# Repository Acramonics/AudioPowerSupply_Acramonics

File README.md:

Audio Power Supply
==================

(c) acramonics July 2026
------------------------

This audio power supply is a simple 15-0-15V supply using a 12-0-12V
transformer. It also provides a version with a 48V rail for phantom
power.

The design is very simple and based on ones from MKS, Jake Rothman and
Douglas Self.

If using a 12-0-12V transformer, then you only need small heatsinks
(as this will provide around 17-0-17V DC), but if using something like
a 15-0-15V transformer, you will need the specified Fischer SK104
heatsinks. The specified 2W resistor (R1) is overkill - around 0.25W
will be produced here, but it does get noticeably warm so the larger
resistor will guard against premature failure.

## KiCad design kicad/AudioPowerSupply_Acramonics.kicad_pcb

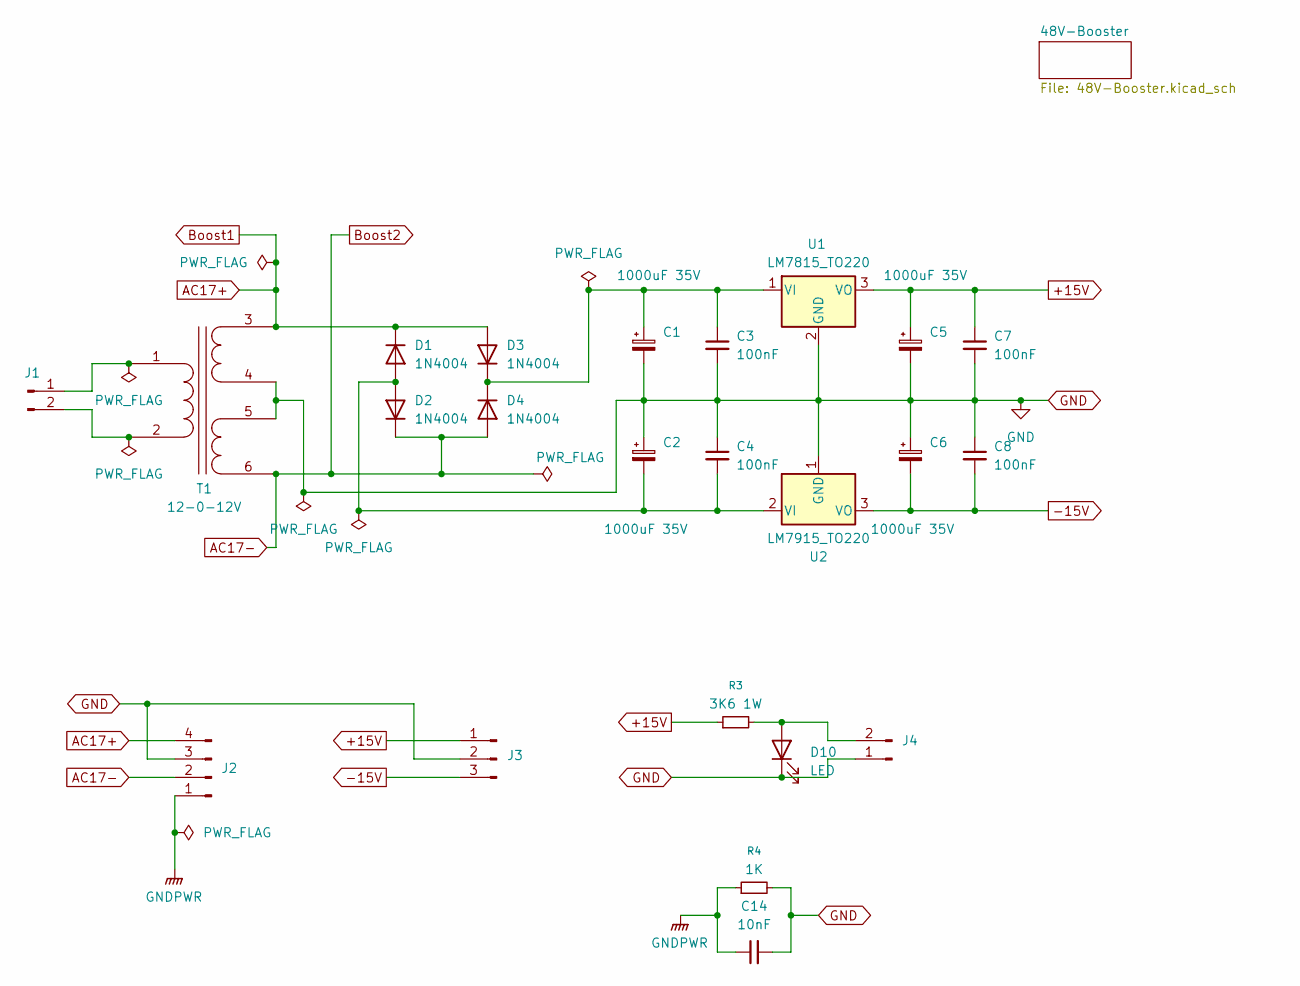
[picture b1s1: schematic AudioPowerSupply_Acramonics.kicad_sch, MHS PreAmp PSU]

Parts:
C1, C2, C5, C6: 1000uF 35V; CP_Radial_D12.5mm_P5.00mm
C3, C4, C7, C8: 100nF; C_Rect_L7.2mm_W3.0mm_P5.00mm_FKS2_FKP2_MKS2_MKP2
C14: 10nF; C_Rect_L7.2mm_W3.0mm_P5.00mm_FKS2_FKP2_MKS2_MKP2
D1, D2, D3, D4: 1N4004; D_DO-41_SOD81_P10.16mm_Horizontal
D10: LED
J1: (no value)
J2: Conn_01x04_Pin; Altech_AK100_1x04_P5.00mm
J3: Altech_AK100_1x03_P5.00mm
J4: Molex_KK-254_AE-6410-02A_1x02_P2.54mm_Vertical
R3: 3K6 1W; R_Axial_DIN0414_L11.9mm_D4.5mm_P15.24mm_Horizontal
R4: 1K; R_Axial_DIN0207_L6.3mm_D2.5mm_P10.16mm_Horizontal
T1: 12-0-12V
U1: LM7815_TO220; TO-220-3_Vertical
U2: LM7915_TO220; TO-220-3_Vertical

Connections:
+15V: C5.1, C7.1, J3.1, R3.1, U1.3 (VO)
-15V: C6.2, C8.2, J3.3, U2.3 (VO)
AC17+: D1.1 (K), D3.2 (A), J2.4, T1.3 (SA); also elsewhere on the board
AC17-: D2.1 (K), D4.2 (A), J2.2, T1.6 (SD); also elsewhere on the board
GND: C1.2, C2.1, C3.2, C4.1, C5.2, C6.1, C7.2, C8.1, C14.2, D10.1 (K), J2.3, J3.2, J4.1, R4.2, T1.4 (SB), T1.5 (SC), U1.2 (GND), U2.1 (GND); also elsewhere on the board
GNDPWR: C14.1, J2.1, R4.1
unnamed: C2.2, C4.2, D1.2 (A), D2.2 (A), U2.2 (VI)
unnamed: C1.1, C3.1, D3.1 (K), D4.1 (K), U1.1 (VI)
unnamed: J1.1, T1.1 (AA)
unnamed: J1.2, T1.2 (AB)
unnamed: D10.2 (A), J4.2, R3.2

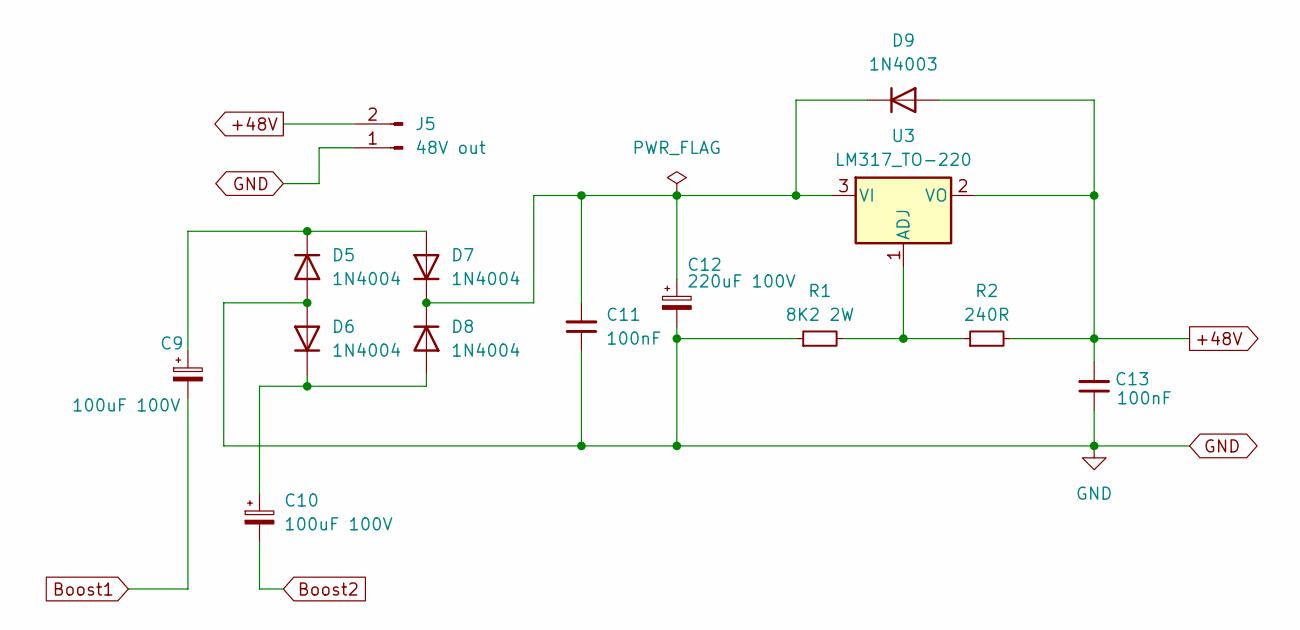
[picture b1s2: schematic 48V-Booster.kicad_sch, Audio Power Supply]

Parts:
C9, C10: 100uF 100V; CP_Radial_D12.5mm_P5.00mm
C11, C13: 100nF; C_Rect_L7.2mm_W3.0mm_P5.00mm_FKS2_FKP2_MKS2_MKP2
C12: 220uF 100V; CP_Radial_D12.5mm_P5.00mm
D5, D6, D7, D8: 1N4004; D_DO-41_SOD81_P10.16mm_Horizontal
D9: 1N4003; D_DO-41_SOD81_P10.16mm_Horizontal
J5: 48V out; Molex_KK-254_AE-6410-02A_1x02_P2.54mm_Vertical
R1: 8K2 2W; R_Axial_DIN0516_L15.5mm_D5.0mm_P25.40mm_Horizontal
R2: 240R; R_Axial_DIN0207_L6.3mm_D2.5mm_P10.16mm_Horizontal
U3: LM317_TO-220; TO-220-3_Vertical

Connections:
+48V: C13.2, D9.2 (A), J5.2, R2.2, U3.2 (VO)
AC17+: C9.2; also elsewhere on the board
AC17-: C10.2; also elsewhere on the board
GND: C11.1, C12.2, C13.1, D5.2 (A), D6.2 (A), J5.1, R1.1; also elsewhere on the board
unnamed: C9.1, D5.1 (K), D7.2 (A)
unnamed: C10.1, D6.1 (K), D8.2 (A)
unnamed: C11.2, C12.1, D7.1 (K), D8.1 (K), D9.1 (K), U3.3 (VI)
unnamed: R1.2, R2.1, U3.1 (ADJ)

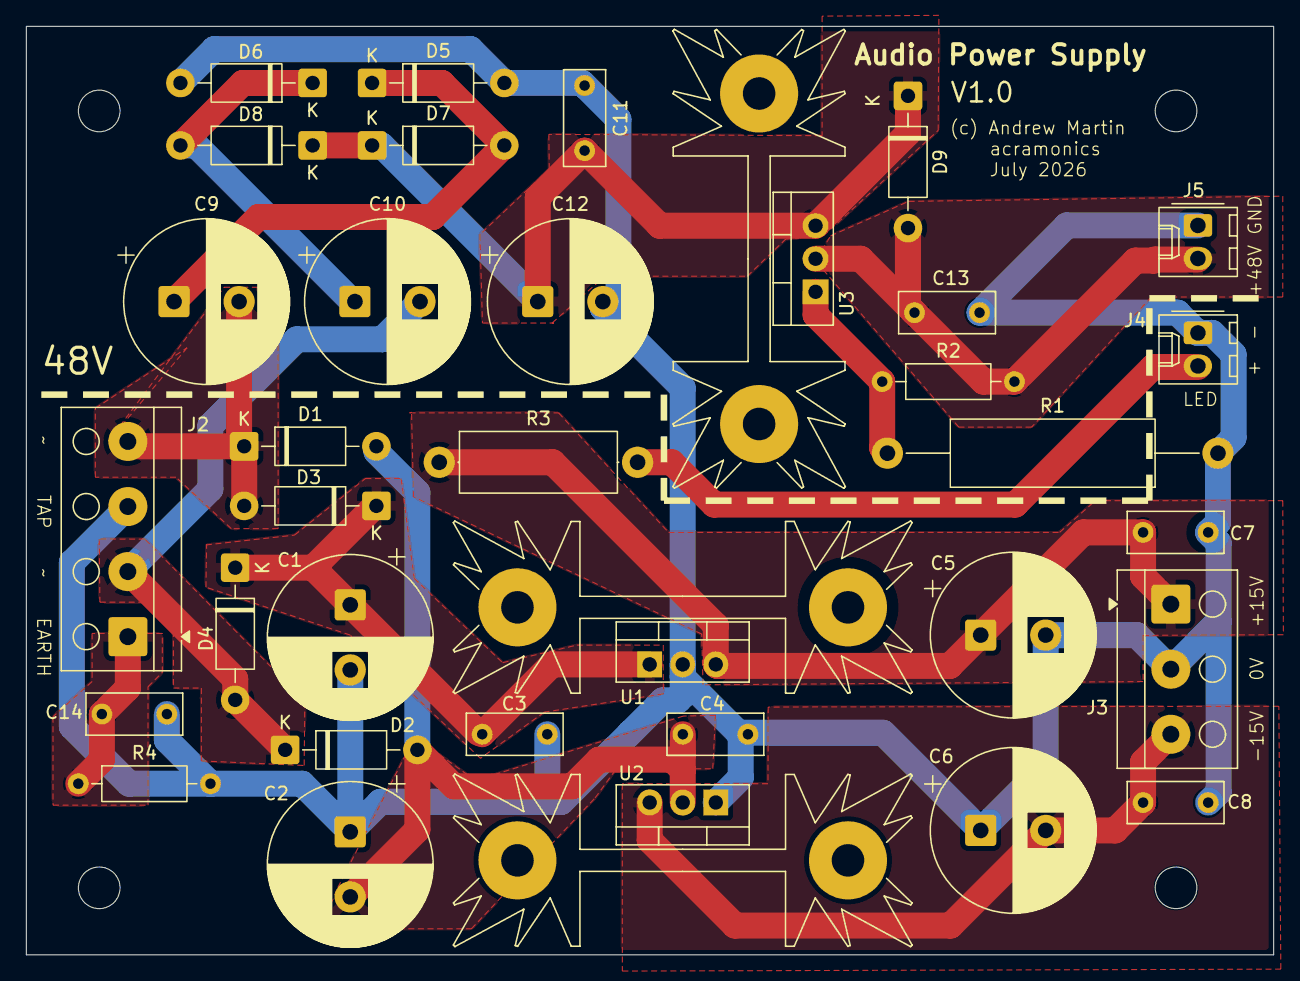
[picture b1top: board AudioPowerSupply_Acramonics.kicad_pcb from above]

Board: 2 copper layers, 95.8 x 71.3 mm, 34 parts (0 on the bottom side), 14 nets.
